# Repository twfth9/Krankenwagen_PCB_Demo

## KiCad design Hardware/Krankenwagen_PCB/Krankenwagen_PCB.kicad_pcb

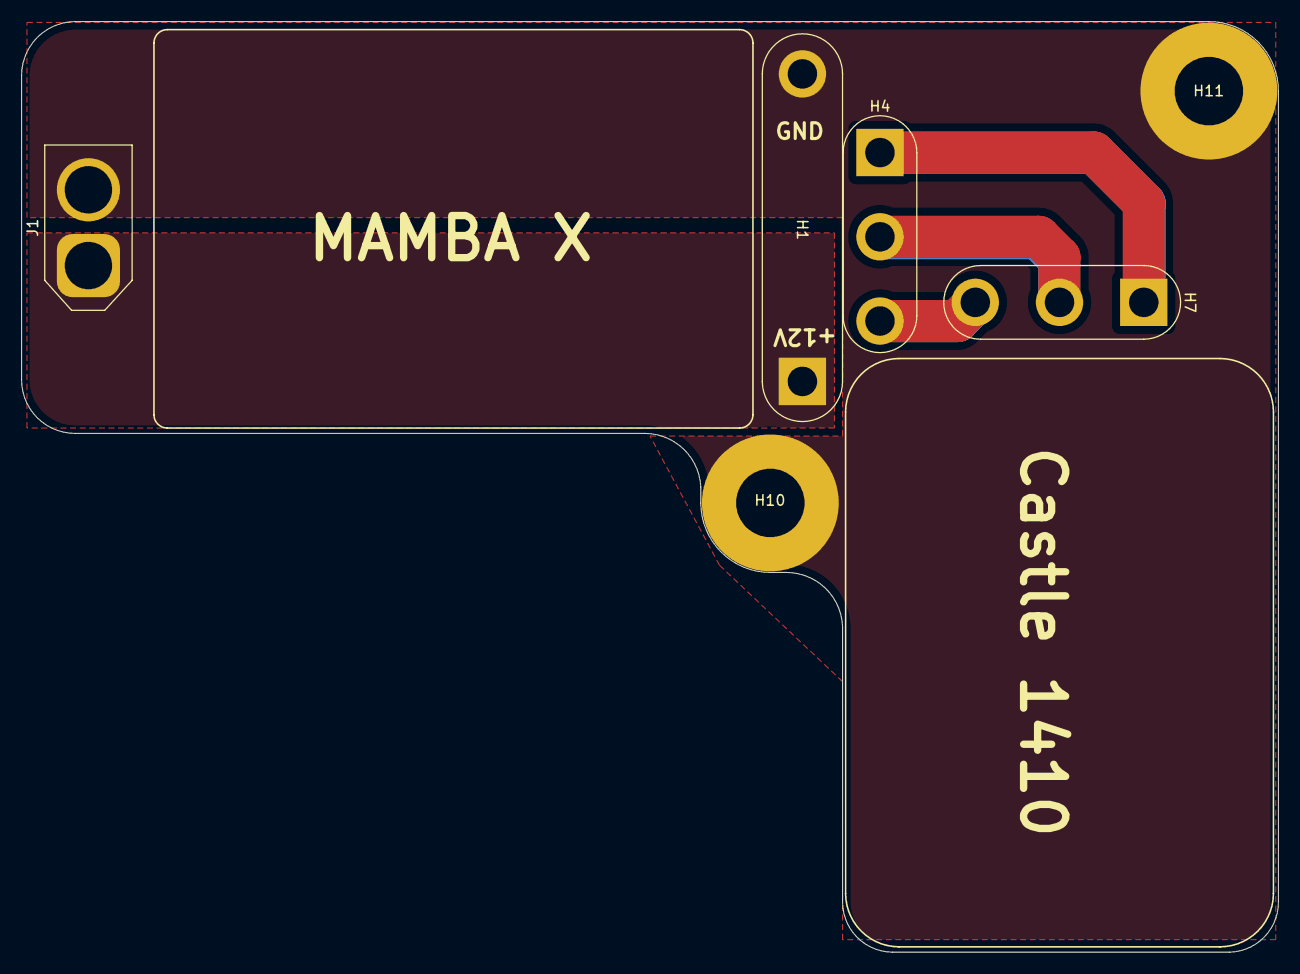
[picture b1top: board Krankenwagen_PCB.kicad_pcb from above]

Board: 2 copper layers, 119.4 x 88.4 mm, 6 parts (0 on the bottom side), 5 nets.

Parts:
H1: 3.5mm Plated Holes; Solder Holes MAMBA X Power
H4, H7: 2.8mm Plated Holes; 2.8mm Solder Hole x3
H10, H11: MountingHole; MountingHole_6.5mm_Pad
J1: XT60-F; AMASS_XT60-F_1x02_P7.20mm_Vertical

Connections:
+12V: H1.1, J1.1
GND: H1.2, H10.1, H11.1, J1.2
unnamed: H4.1, H7.1
unnamed: H4.2, H7.2
unnamed: H4.3, H7.3

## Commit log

2022-10-02 Start of schematic, added documentation
2022-10-02 Completed schematic
2022-10-02 Created solder hole footprints
2022-10-02 Added XT60 footprints, assigned footprints
2022-10-02 Basic PCB completed, added logos to silkscreen
2022-10-02 Added mounting holes to PCB and Schematic
2022-10-02 Generated step file of PCB
2022-10-02 Added title page info to PCB file
